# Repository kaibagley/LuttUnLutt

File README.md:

### 

3x5+2 key split orthogonal BLE keyboard

This fork is a custom version of weteor's Lütt un Lütt, altered such that it is powered by a pair of LiPO batteries rather than coin cells, and uses MX switches.

## Features

- Diode-less pcb, since there are enough GPIO pins on the nice!nano
- full BLE, powered by 3.7v 110mAh LiPO batteries
- MX hotswap sockets
- case files are supplied (stl, dxf, as well as the freecad files)
- supports both nice!nano and pro micro
- QMK, ZMK, etc. support with pro micro, or ZMK with nice!nano

## Prototype

- First prototype printed on 18th March 2023

## what's left to do?

- fix small hole placement error in case
- implement support of Elite-C/Pi
- add mounting holes

## Credit

This repo is inspired by weteor's Lütt un Lütt, please visit this link: https://github.com/weteor/LuttUnLutt to view the original, and support the creator.

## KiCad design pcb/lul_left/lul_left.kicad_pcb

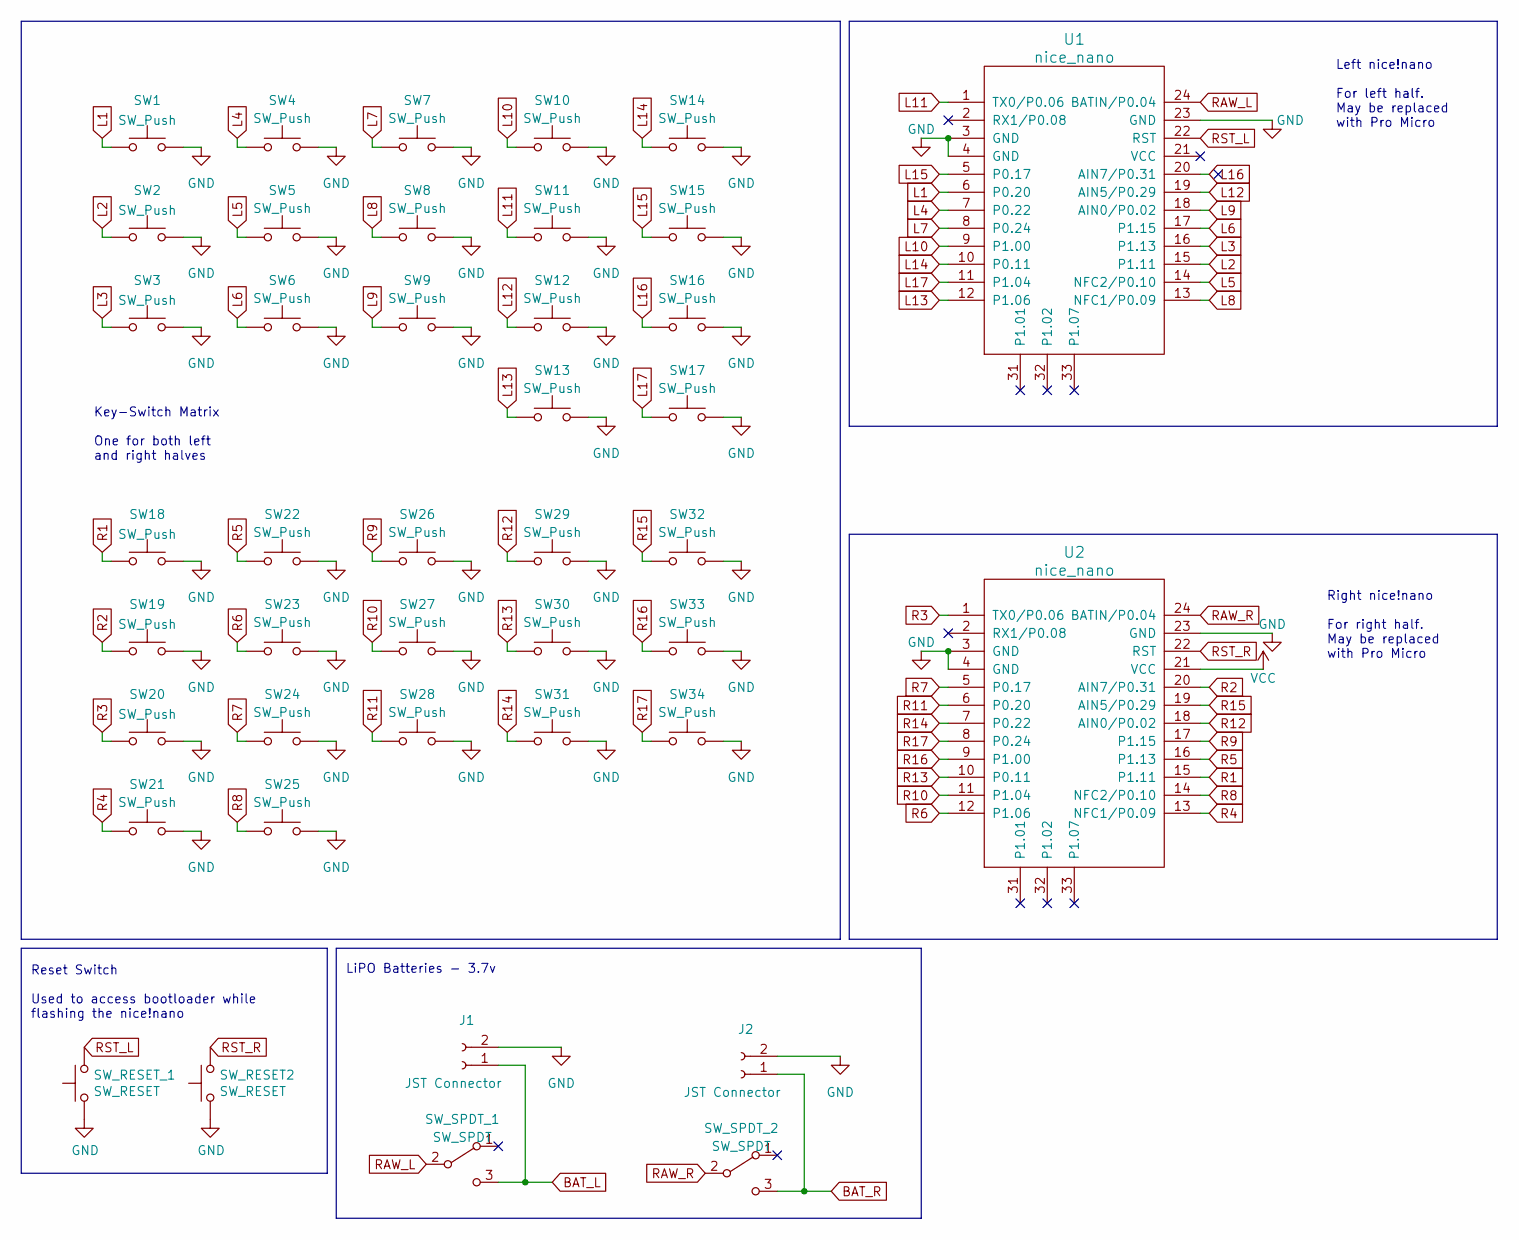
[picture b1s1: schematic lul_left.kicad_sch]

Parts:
J1, J2: JST Connector; JST_PH_S2B-PH-K_1x02_P2.00mm_Horizontal
SW1, SW2, SW3, SW4, SW5, SW6, SW7, SW8, SW9, SW10, SW11, SW12, SW14, SW15, SW16, SW17, SW18, SW19, SW20, SW22, SW23, SW24, SW25, SW26, SW27, SW28, SW29, SW30, SW31, SW32, SW33, SW34: SW_Push; MXOnly-1U-Hotswap
SW13, SW21: SW_Push; MXOnly-1.75U-Hotswap
SW_RESET2: SW_RESET; SKQG-1155865
SW_RESET_1: SW_RESET; SKQG-1155865
SW_SPDT_1, SW_SPDT_2: SW_SPDT; SW_SPDT_PCM12
U1, U2: nice_nano

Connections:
BAT_L: J1.1, SW_SPDT_1.3 (C)
BAT_R: J2.1, SW_SPDT_2.3 (C)
GND: J1.2, J2.2, SW1.2, SW2.2, SW3.2, SW4.2, SW5.2, SW6.2, SW7.2, SW8.2, SW9.2, SW10.2, SW11.2, SW12.2, SW13.2, SW14.2, SW15.2, SW16.2, SW17.2, SW18.2, SW19.2, SW20.2, SW21.2, SW22.2, SW23.2, SW24.2, SW25.2, SW26.2, SW27.2, SW28.2, SW29.2, SW30.2, SW31.2, SW32.2, SW33.2, SW34.2, SW_RESET2.1, SW_RESET_1.1, U1.3 (GND), U1.4 (GND), U1.23 (GND), U2.3 (GND), U2.4 (GND), U2.23 (GND)
L1: SW1.1, U1.6 (P0.20)
L2: SW2.1, U1.15 (P1.11)
L3: SW3.1, U1.16 (P1.13)
L4: SW4.1, U1.7 (P0.22)
L5: SW5.1, U1.14 (NFC2/P0.10)
L6: SW6.1, U1.17 (P1.15)
L7: SW7.1, U1.8 (P0.24)
L8: SW8.1, U1.13 (NFC1/P0.09)
L9: SW9.1, U1.18 (AIN0/P0.02)
L10: SW10.1, U1.9 (P1.00)
L11: SW11.1, U1.1 (TX0/P0.06)
L12: SW12.1, U1.19 (AIN5/P0.29)
L13: SW13.1, U1.12 (P1.06)
L14: SW14.1, U1.10 (P0.11)
L15: SW15.1, U1.5 (P0.17)
L16: SW16.1, U1.20 (AIN7/P0.31)
L17: SW17.1, U1.11 (P1.04)
R1: SW18.1, U2.15 (P1.11)
R2: SW19.1, U2.20 (AIN7/P0.31)
R3: SW20.1, U2.1 (TX0/P0.06)
R4: SW21.1, U2.13 (NFC1/P0.09)
R5: SW22.1, U2.16 (P1.13)
R6: SW23.1, U2.12 (P1.06)
R7: SW24.1, U2.5 (P0.17)
R8: SW25.1, U2.14 (NFC2/P0.10)
R9: SW26.1, U2.17 (P1.15)
R10: SW27.1, U2.11 (P1.04)
R11: SW28.1, U2.6 (P0.20)
R12: SW29.1, U2.18 (AIN0/P0.02)
R13: SW30.1, U2.10 (P0.11)
R14: SW31.1, U2.7 (P0.22)
R15: SW32.1, U2.19 (AIN5/P0.29)
R16: SW33.1, U2.9 (P1.00)
R17: SW34.1, U2.8 (P0.24)
RAW_L: SW_SPDT_1.2 (B), U1.24 (BATIN/P0.04)
RAW_R: SW_SPDT_2.2 (B), U2.24 (BATIN/P0.04)
RST_L: SW_RESET_1.2, U1.22 (RST)
RST_R: SW_RESET2.2, U2.22 (RST)
VCC: U2.21 (VCC)

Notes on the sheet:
Key-Switch Matrix One for both left and right halves
LiPO Batteries - 3.7v
Right nice!nano For right half. May be replaced with Pro Micro
Reset Switch Used to access bootloader while flashing the nice!nano
Left nice!nano For left half. May be replaced with Pro Micro

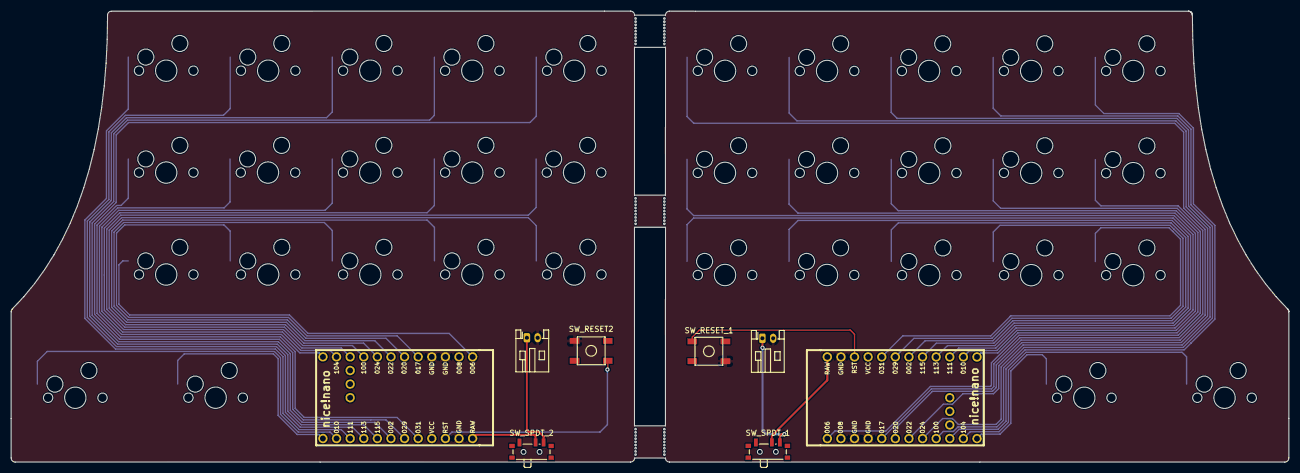
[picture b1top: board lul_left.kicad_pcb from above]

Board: 2 copper layers, 238.5 x 84.2 mm, 44 parts (0 on the bottom side), 41 nets.

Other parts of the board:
G1, G2: LOGO

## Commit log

2023-03-15 added libraries and a few edits to schematic
2023-03-15 remove submodules
2023-03-15 Add nice!nano, add on/off switch
2023-03-16 Fixed switch count
2023-03-16 add controllers for both keyswitch matrices
2023-03-17 remove license
2023-03-17 Create LICENSE
2023-03-17 switches positioned properly
2023-03-17 change schematic to be diode-less
2023-03-17 move components to temporary locations
2023-03-18 move components, add dimension labels, add breakable tabs between pcb bodies
2023-03-18 touch up dimensions and positions
2023-03-18 route switches nicely
2023-03-18 route fully. Just need ground fill
2023-03-18 remove the old fill zones
2023-03-18 add full grounded copper fills to top and bottom layers
2023-03-18 add randomly placed vias to remove any potential capacitance between the copper fills? probably not necessary but i feel like im using my physics degree by doing this
2023-03-18 fix small connection issue
2023-03-18 edge cuts fixed
2023-03-18 fix footprint courtyard error in MX_1U and MX_1.75U
2023-03-30 Add case and plate
2023-04-04 updated case
2023-04-04 updated case bottom
